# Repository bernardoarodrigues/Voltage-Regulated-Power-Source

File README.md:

# Voltage Regulator Power Supply Project

## Description
Rectifier power supply that converts alternating current with an effective voltage of 127V into direct current with an adjustable voltage between 3V and 12V.

## Group
 - [Bernardo Alexandre Alves Rodrigues](mailto:bernardorodrigues@usp.br)
 - [Gabriel Phelippe Prado](mailto:gabriel.phelippe@usp.br)
 - [Gabriel Campanelli Iamato](mailto:gabriel.c.iamato@usp.br)
 - [Henrique Vieira Lima](mailto:vieira.henrique@usp.br)

## Information
 - **Course:** Electronics for Computing
 - **Professor:** Eduardo do Valle Simões
 - **Degree:** Bachelor’s in Computer Science
 - **Class:** BCC-A / 2024 

## Project
 - Watch the project in action in this [video](https://youtu.be/LmAK9lCr3QM)

 - Watch the project explanation in this [video](https://youtu.be/v0-GvNXRQ9Q?si=ZIwsNRWMdKinU6Kj)

## Prototype
 - Watch the project explanation in this [vídeo](https://youtu.be/MAERgxqwMdY?si=GL7MvnJlF9lUfxt0)

## Component List
| Quantity | Components        | Price (R$) |
|----|---------------|------------|
| 1x | Fuse                   | R$1,00 |
| 1x | Varistor               | R$2,40 |
| 1x | Transformer 12V 0.5A   | R$41,00 |
| 4x | Diode 1N4001           | R$0,19 x 4 = R$0,76 |
| 1x | Capacitor 1mF 35V      | R$2,00 |
| 1x | Red LED 5mm            | R$0,45 |
| 1x | Resistor 2.2k          | R$0,07 |
| 1x | Resistor 8.2k          | R$0,07 |
| 1x | Resistor 470           | R$0,72 |
| 1x | Trimpot 500            | R$2,81 |
| 1x | Zener Diode 13V 0.5W   | R$0,35 |
| 1x | Potentiometer 5k       | R$6,70 |
| 1x | Transistor TIP 31 C    | R$3,70 |
| 1x | Push Button Switch     | R$2,90 |
| 2x | 2-pin Terminal Block   | R$2,20 |
| 1x | USB-A Connector        | R$3,30 |
| 1x | Phenolic Board         | R$7,80 |
| 1x | AC Plug 10A            | R$5,80 |
| 1x | Wire 0,5mm             | R$4,50 |
| **Total** |                 | **R$88,53** |

 - Components purchased from [Ca And Ma](https://www.caandma.com.br/) in São Carlos/SP.

## Component Functionality
 - **Fuse:** A safety device that interrupts the flow of electrical current in a circuit when it exceeds the allowed limit, protecting the circuit against current surges.
 - **Varistor:** An electronic component whose resistance varies according to the voltage applied to its terminals. As the voltage increases, the resistance decreases. Varistors are used to protect electronic devices from voltage spikes.
 - **Transformer:** A device that uses electromagnetic induction to increase or decrease electrical voltage while maintaining power. Transformers work exclusively with alternating current. In the rectifier circuit, the transformer reduces the 127V (from the wall outlet) to 24V.
 - **Diode Bridge:** Converts alternating current (AC) into direct current (DC). It consists of four rectifier diodes connected in a specific configuration that allows current to flow in only one direction.
 - **Capacitor:** Stores electrical charge. In the regulator, during the AC cycles, it releases current when its internal voltage is greater than the voltage from the diode bridge. It discharges when the cycle inverts. The capacitor was selected for a desired ripple of 10%. After calculations, a capacitance of 416.7µF was obtained. Thus, we chose the commercial value of 470µF.
 - **Led:** A diode that converts electricity into light. In this circuit, it indicates when the power supply is turned on.
 - **Resistors:** Electronic components that regulate the amount of electricity flowing through a circuit. They decrease the current intensity and reduce voltage along a wire.
 - **Zener Diode:** A component that regulates the maximum voltage. It conducts current only when the input voltage reaches its nominal voltage, in this project 12V. If the voltage is below 12V, no current passes through the Zener diode, so it does not affect the circuit.
 - **Potentiometer:** An adjustable resistor. It allows selecting the output voltage, between 3V and 12V.
 - **NPN Transistor:** A semiconductor device that can amplify electrical currents, generate oscillations, and more. In this project, it allows the adjustable flow of current.
 - **Switch:** An electrical switch can be either closed or open. When closed, current flows through the circuit; when open, it does not. This enables turning the power supply on and off.

## Circuit Simulation - Falstad
 - Access the simulation via this [link](https://tinyurl.com/2fm74n5c)
 - Or, in the menu `File > Import from Text` of [Falstad](https://falstad.com/circuit/circuitjs.html), open the file `./Arquivos/circuitoFalstad.txt` from the repo

## Circuit Schematic - Eagle
 - Download [Eagle](https://www.autodesk.com/products/eagle/overview)
 - In the menu `File > Open > Schematic...`, open the file `./Arquivos/esquematicoEagle.sch` from the repo

## PCB - Eagle
 - Download [Eagle](https://www.autodesk.com/products/eagle/overview)
 - In the menu `File > Open > Schematic...`, open the file `./Arquivos/pcbEagle.brd` from the repo
<div style="width: 100%; text-align: center;" align="center">

</div>

## License
This project is licensed under the GNU General Public License V3.0, published by the Free Software Foundation.

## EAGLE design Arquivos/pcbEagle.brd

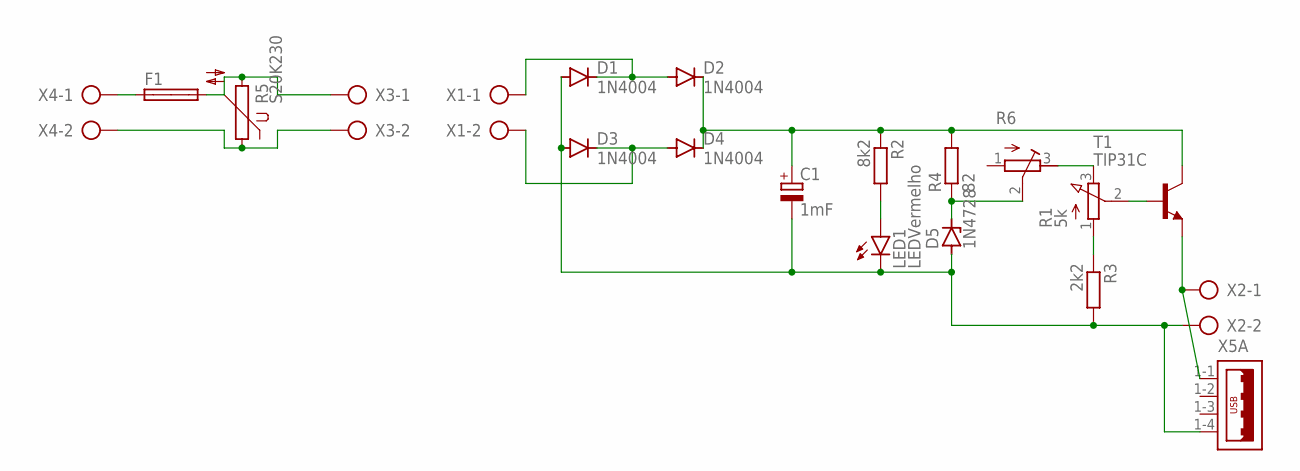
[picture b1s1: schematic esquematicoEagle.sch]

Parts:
C1: 1mF; E5-10,5
D1, D2, D3, D4: 1N4004; DO41-10
D5: 1N4728; DO41Z10
F1: SHK20L
LED1: LEDVermelho; LED5MM
R1: 5k; 3RP/1610N
R2: 8k2; 0204/7
R3: 2k2; 0204/7
R4: 82; 0204/7
R5: S20K230
R6: R-TRIMM3296W; RTRIM3296W
T1: TIP31C; TO220
X1, X2, X3, X4: AK500/2-H
X5: USB_4-32003-40XA; 32003-40XA

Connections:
unnamed: C1.-, D1.A, D3.A, D5.A, LED1.K (C), R3.2, X2.2, X5.1-4 (4)
unnamed: D1.C, D2.A, X1.1
unnamed: C1.+, D2.C, D4.C, R2.1, R4.2, T1.2 (C)
unnamed: D3.C, D4.A, X1.2
unnamed: LED1.A, R2.2
unnamed: D5.C, R4.1, R6.2 (S)
unnamed: R1.3 (E), R6.3 (E)
unnamed: R1.1 (A), R3.1
unnamed: R1.2 (S), T1.1 (B)
unnamed: T1.3 (E), X2.1, X5.1-1 (1)
unnamed: F1.1A, X4.1
unnamed: R5.1, X3.2, X4.2
unnamed: F1.2A, R5.2, X3.1

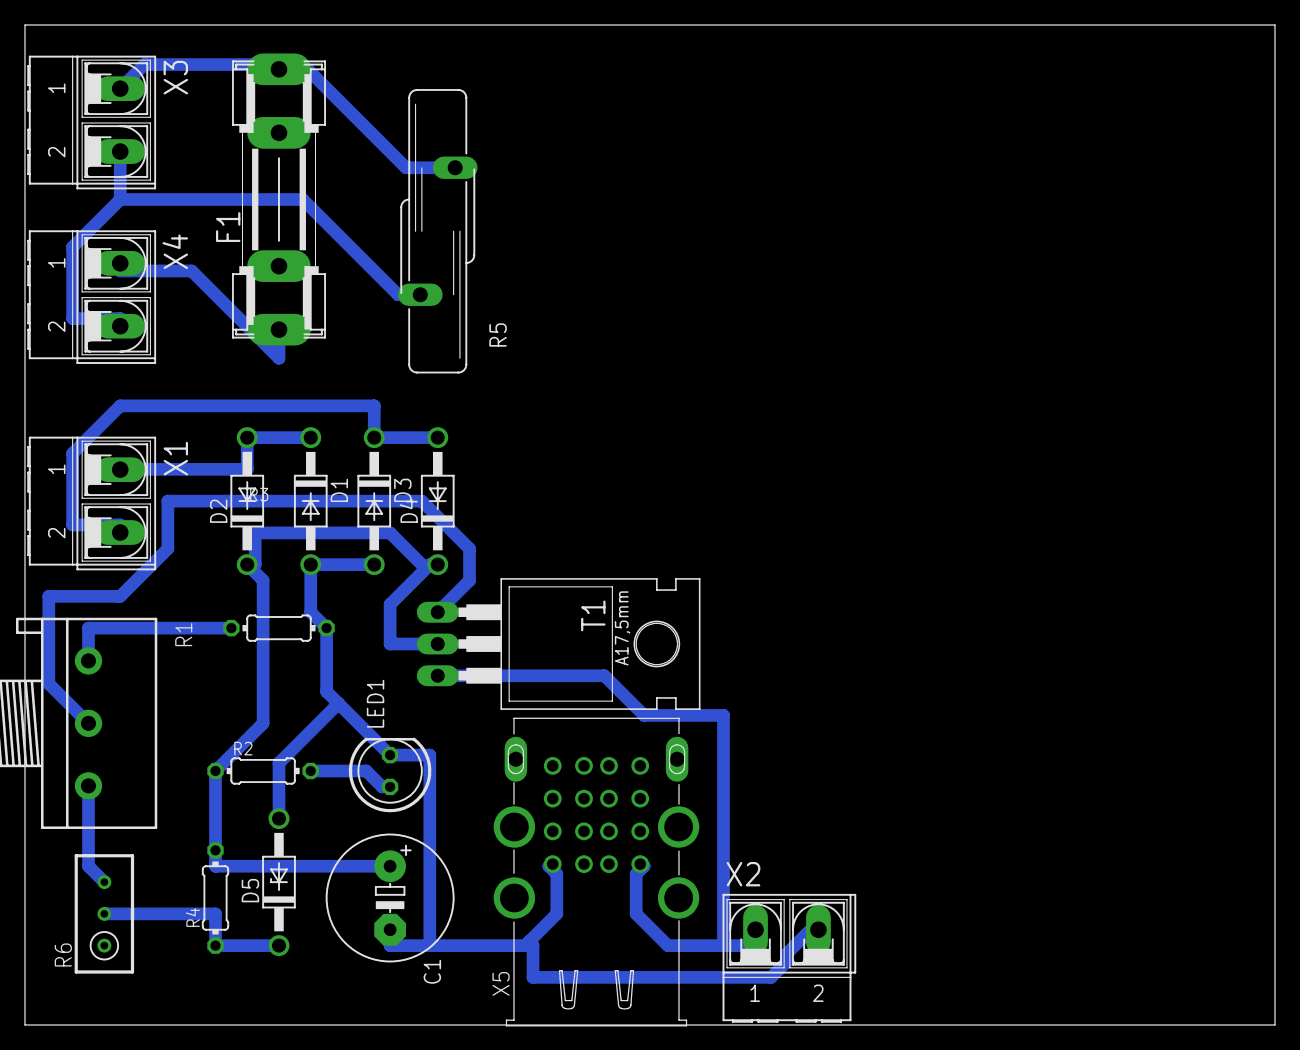
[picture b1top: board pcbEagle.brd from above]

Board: 2 copper layers, 100.0 x 80.0 mm, 20 parts (0 on the bottom side), 13 nets.

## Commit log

2024-05-14 Added README.md
2024-05-14 Added Falstad files
2024-05-28 Changed falstad circuit
2024-05-28 Added prototype media
2024-05-28 Changed list of items
2024-06-10 Added Eagle files and small changes in readme
2024-06-15 Small changes in component list
2024-06-25 Added explanation video
2024-06-25 Small change in falstad circuit
2024-06-26 Small changes in falstad and readme
2024-06-26 Changed falstad link
2025-09-02 Translated README to English
